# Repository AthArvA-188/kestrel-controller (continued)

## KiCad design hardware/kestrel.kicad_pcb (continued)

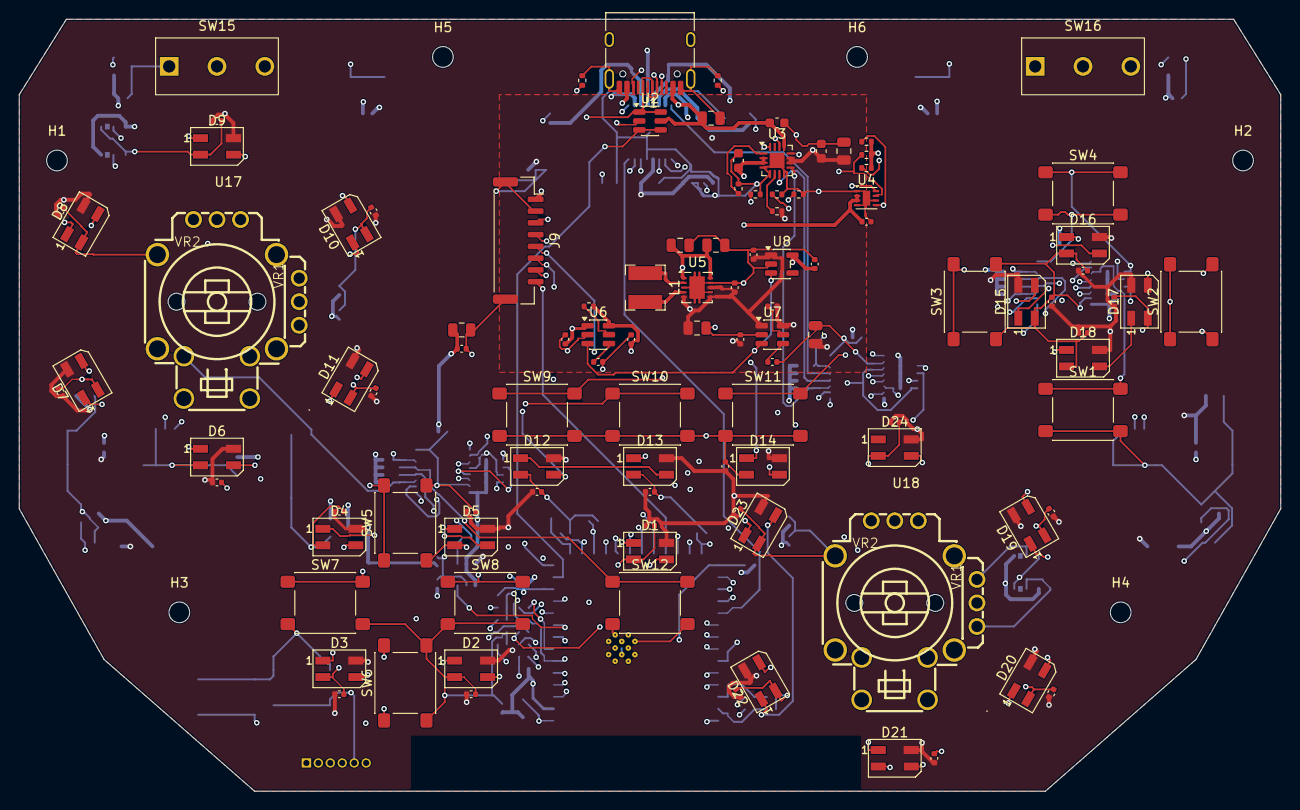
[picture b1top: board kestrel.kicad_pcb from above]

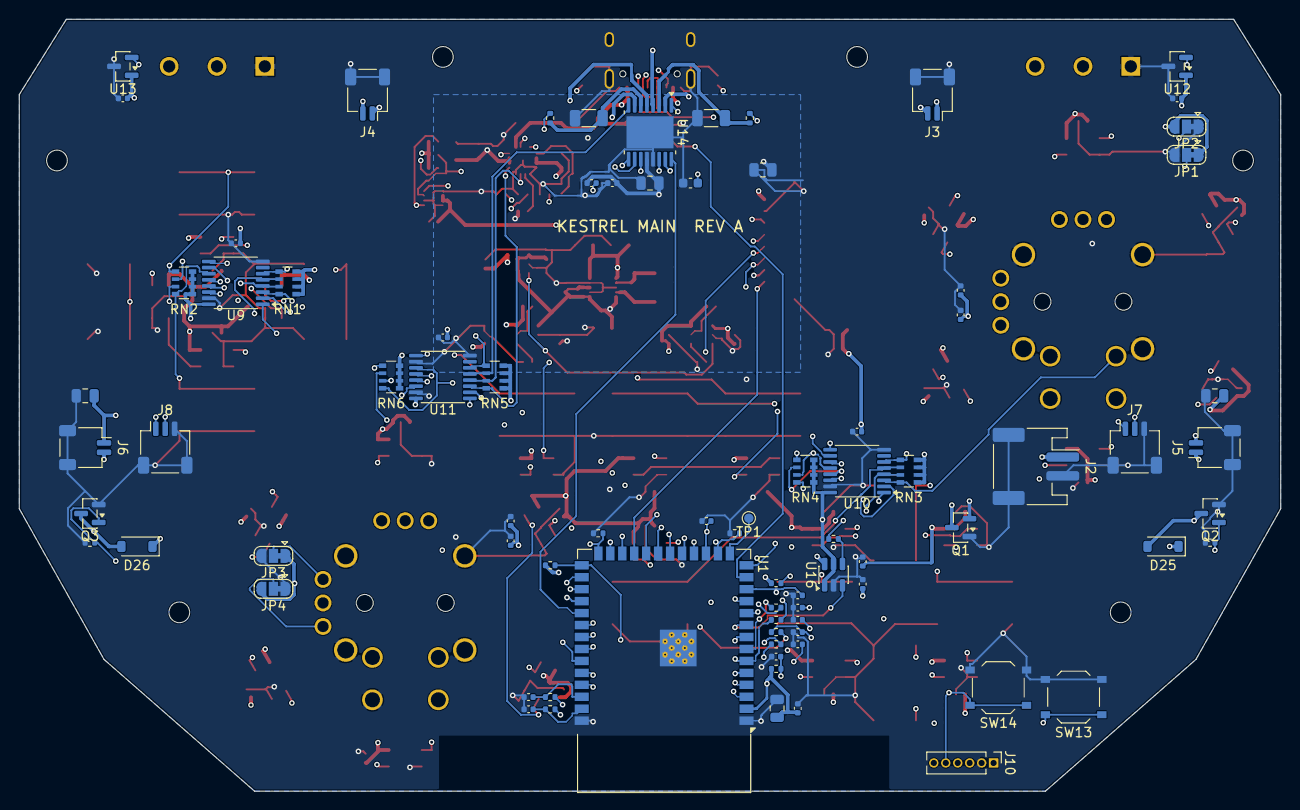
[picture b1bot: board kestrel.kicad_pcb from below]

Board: 4 copper layers, 134.0 x 82.0 mm, 193 parts (81 on the bottom side), 130 nets.

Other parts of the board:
H1, H2, H3, H4, H5, H6: M2; MountingHole_2.2mm_M2

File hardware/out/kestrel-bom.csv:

Qty,References,Value,Footprint,MPN
1,J1,USB-C,USB_C_Receptacle_HRO_TYPE-C-31-M-12,TYPE-C-31-M-12
2,R1 R2,5.1k,R_0402_1005Metric,
1,U2,USBLC6-2SC6,SOT-23-6,USBLC6-2SC6
1,C1,10u 25V,C_0805_2012Metric,
1,U3,BQ24074,VQFN-16-1EP_3x3mm_P0.5mm_EP1.6x1.6mm,BQ24074RGTR
3,C2 C3 C5,4.7u,C_0603_1608Metric,
7,C4 C7 C8 C9 C15 C36 C72,10u,C_0805_2012Metric,
1,R3,887,R_0402_1005Metric,
1,R4,1.13k,R_0402_1005Metric,
1,R5,68k,R_0402_1005Metric,
6,R6 R7 R10 R13 R14 R15,10k,R_0402_1005Metric,
1,J2,BAT,JST_PH_S2B-PH-SM4-TB_1x02-1MP_P2.00mm_Horizontal,S2B-PH-SM4-TB
1,Q1,AO3401A,SOT-23,AO3401A
1,U4,MAX17048,DFN-8-1EP_2x2mm_P0.5mm_EP0.8x1.6mm,MAX17048G+T10
46,C6 C10 C20 C22 C23 C24 C25 C26 C27 C28 C29 C31 C33 C34 C35 C37 C43 C44 C45 C46 C47 C48 C49 C50 C51 C52 C53 C54 C55 C56 C57 C58 C59 C60 C61 C62 C63 C64 C65 C66 C67 C68 C69 C70 C71 C73,100n,C_0402_1005Metric,
2,R8 R9,4.7k,R_0402_1005Metric,
1,U5,TPS63001,Texas_DRC0010J,TPS63001DRCR
1,L1,2.2u,L_Bourns-SRN4018,SRN4018-2R2M
2,U6 U7,TPS22917,SOT-23-6,TPS22917DBVR
2,R11 R12,220,R_0402_1005Metric,
8,C11 C12 C14 C17 C18 C21 C30 C32,1u,C_0402_1005Metric,
2,C13 C16,1n,C_0402_1005Metric,
1,U8,TLV70030,SOT-23-5,TLV70030DDCR
1,U1,ESP32-S3-WROOM-1-N16R2,ESP32-S3-WROOM-1,ESP32-S3-WROOM-1-N16R2
4,C19 C40 C41 C42,22u,C_0805_2012Metric,
4,R16 R17 R28 R29,100k,R_0402_1005Metric,
2,SW13 SW14,BOOT,SW_Push_1P1T_XKB_TS-1187A,TS-1187A-B-A-B
1,J10,DEBUG,PinHeader_1x06_P1.27mm_Vertical,
8,R18 R19 R20 R21 R22 R23 R24 R25,1k,R_0402_1005Metric,
2,U17 U18,TMR stick,SW-TH_RKJXV1224005,"TMR module, RKJXV1224005 footprint"
2,U12 U13,DRV5055A4,SOT-23,DRV5055A4QDBZR
1,U14,DRV8833,HTSSOP-16-1EP_4.4x5mm_P0.65mm_EP3.4x5mm_Mask2.46x2.31mm,DRV8833PWPR
2,R26 R27,0.2 1%,R_1206_3216Metric,
1,C38,2.2u,C_0603_1608Metric,
1,C39,10n,C_0402_1005Metric,
4,J3 J4 J5 J6,TRIG_L,JST_SH_SM02B-SRSS-TB_1x02-1MP_P1.00mm_Horizontal,SM02B-SRSS-TB
2,Q2 Q3,AO3400A,SOT-23,AO3400A
2,D25 D26,B5819W,D_SOD-123,B5819W
2,J7 J8,PADDLE_L,JST_SH_SM03B-SRSS-TB_1x03-1MP_P1.00mm_Horizontal,SM03B-SRSS-TB
3,U9 U10 U11,74HC165,TSSOP-16_4.4x5mm_P0.65mm,SN74HC165PWR
6,RN1 RN2 RN3 RN4 RN5 RN6,10k,R_Array_Convex_4x0603,YC164-JR-0710KL
12,SW1 SW2 SW3 SW4 SW5 SW6 SW7 SW8 SW9 SW10 SW11 SW12,A,SW_SPST_PTS645Sx43SMTR92,PTS645SM43SMTR92
2,SW15 SW16,LB,SW_D2FC_THT,D2FC-F-7N
1,U16,SN74LVC1T45,SOT-23-6,SN74LVC1T45DBVR
1,R30,330,R_0402_1005Metric,
24,D1 D2 D3 D4 D5 D6 D7 D8 D9 D10 D11 D12 D13 D14 D15 D16 D17 D18 D19 D20 D21 D22 D23 D24,FN,LED_SK6812MINI_PLCC4_3.5x3.5mm_P1.75mm,SK6812MINI
1,J9,LCD,JST_GH_SM08B-GHS-TB_1x08-1MP_P1.25mm_Horizontal,SM08B-GHS-TB

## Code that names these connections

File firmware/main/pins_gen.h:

// Generated by tools/gen_pins.py from shared/pinmap.json. Do not edit.

#pragma once

#define PIN_BOOT 0
#define PIN_STICK_LX 1
#define ADC_CH_STICK_LX 0
#define PIN_STICK_LY 2
#define ADC_CH_STICK_LY 1
#define PIN_TP_GPIO3 3
#define PIN_STICK_RX 4
#define ADC_CH_STICK_RX 3
#define PIN_STICK_RY 5
#define ADC_CH_STICK_RY 4
#define PIN_TRIG_L_POS 6
#define ADC_CH_TRIG_L_POS 5
#define PIN_TRIG_R_POS 7
#define ADC_CH_TRIG_R_POS 6
#define PIN_TRIG_L_ISEN 8
#define ADC_CH_TRIG_L_ISEN 7
#define PIN_TRIG_R_ISEN 9
#define ADC_CH_TRIG_R_ISEN 8
#define PIN_LCD_CS 10
#define PIN_LCD_MOSI 11
#define PIN_LCD_SCLK 12
#define PIN_LCD_DC 13
#define PIN_LCD_RST 14
#define PIN_BTN_HOME 15
#define PIN_LED_DATA 16
#define PIN_RUMBLE_L 17
#define PIN_RUMBLE_R 18
#define PIN_USB_DM 19
#define PIN_USB_DP 20
#define PIN_LCD_BL 21
#define PIN_SR_LOAD 35
#define PIN_SR_CLK 36
#define PIN_SR_DATA 37
#define PIN_TRIG_L_IN1 38
#define PIN_TRIG_L_IN2 39
#define PIN_TRIG_R_IN1 40
#define PIN_TRIG_R_IN2 41
#define PIN_FUEL_ALRT_N 42
#define PIN_UART0_TX 43
#define PIN_UART0_RX 44
#define PIN_PERIPH_EN 45
#define PIN_MOTOR_NSLEEP 46
#define PIN_I2C_SDA 47
#define PIN_I2C_SCL 48

#define LCD_WIDTH 320
#define LCD_HEIGHT 170
#define LCD_RAM_OFFSET 35
#define LCD_SPI_HZ 40000000
#define LCD_SPI_MODE 0
#define I2C_BUS_HZ 400000
#define I2C_ADDR_MAX17048 0x36

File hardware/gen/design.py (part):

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    # ---- Battery connector, reverse-polarity FET, fuel gauge ----
    d.add("J2", "Connector_Generic_MountingPin:Conn_01x02_MountingPin", "BAT",
          "Connector_JST:JST_PH_S2B-PH-SM4-TB_1x02-1MP_P2.00mm_Horizontal",
          {"Pin_1": "VBAT_RAW", "Pin_2": "GND", "MountPin": "GND"},
          at=(-41, -5.5, 270), side="B", block="battery", mpn="S2B-PH-SM4-TB")
    d.add("Q1", "Transistor_FET:AO3401A", "AO3401A", "Package_TO_SOT_SMD:SOT-23",
          {"G": "GND", "S": "VBAT", "D": "VBAT_RAW"},
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          {"1": "EN", "2": "GND"}, at=(-37, -29, 0), side="B", block="mcu", mpn="TS-1187A-B-A-B")
    d.add("J10", "Connector_Generic:Conn_01x06", "DEBUG",
          "Connector_PinHeader_1.27mm:PinHeader_1x06_P1.27mm_Vertical",
          {"Pin_1": "3V3", "Pin_2": "GND", "Pin_3": "UART0_TX", "Pin_4": "UART0_RX",
           "Pin_5": "EN", "Pin_6": "BOOT"},
          at=(-36.5, -37, 270), side="B", block="mcu")
    d.add("TP1", "Connector:TestPoint", "GPIO3", "TestPoint:TestPoint_Pad_D1.0mm",
          {"1": "TP_GPIO3"}, at=(-10.5, -11, 0), side="B", block="mcu")

    # ---- Analogue input filters next to the module ----
    rows = [("STICK_RX", -24.4), ("STICK_RY", -23.1), ("TRIG_L_POS", -21.8),
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        d.C("22u", "VLED", (sx * 60, 2, 0), "B", "rumble", "0805")
        d.add(jr, "Connector_Generic_MountingPin:Conn_01x02_MountingPin", "RUMBLE_" + tag,
              "Connector_JST:JST_SH_SM02B-SRSS-TB_1x02-1MP_P1.00mm_Horizontal",
              {"Pin_1": "VLED", "Pin_2": drain, "MountPin": "GND"},
              at=(sx * 60, -3.5, 90 if sx < 0 else 270), side="B", block="rumble", mpn="SM02B-SRSS-TB")
        d.add(jp, "Connector_Generic_MountingPin:Conn_01x03_MountingPin", "PADDLE_" + tag,
              "Connector_JST:JST_SH_SM03B-SRSS-TB_1x03-1MP_P1.00mm_Horizontal",
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             ("U11", "SR3", "SR_Q2", "GND", (22, 4), ("RN5", "RN6")))
    for ref, key, q7, ds, (x, y), packs in chain:
        inputs = [sr[key][letter] for letter in "ABCDEFGH"]
        pins = {"~{PL}": "SR_LOAD", "CP": "SR_CLK", "~{CE}": "GND", "VCC": "3V3_PERIPH",
                "GND": "GND", "Q7": q7, "~{Q7}": NC, "DS": ds}
        for i, net in enumerate(inputs):
            pins["D%d" % i] = net
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    # ---- Display module connector ----
    d.add("J9", "Connector_Generic_MountingPin:Conn_01x08_MountingPin", "LCD",
          "Connector_JST:JST_GH_SM08B-GHS-TB_1x08-1MP_P1.25mm_Horizontal",
          {"Pin_1": "3V3_PERIPH", "Pin_2": "GND", "Pin_3": "LCD_MOSI", "Pin_4": "LCD_SCLK",
           "Pin_5": "LCD_CS", "Pin_6": "LCD_DC", "Pin_7": "LCD_RST", "Pin_8": "LCD_BL",
           "MountPin": "GND"},
          at=(-14, 18.5, 270), block="display", mpn="SM08B-GHS-TB")
    d.C("10u", "3V3_PERIPH", (-20, 9, 0), "F", "display", "0805")
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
